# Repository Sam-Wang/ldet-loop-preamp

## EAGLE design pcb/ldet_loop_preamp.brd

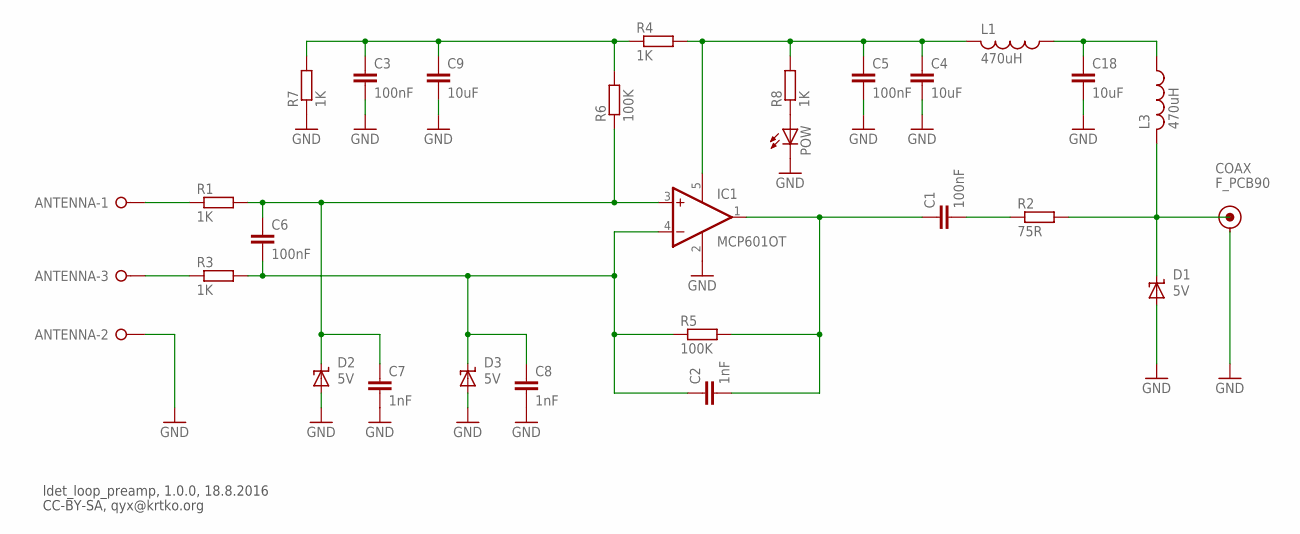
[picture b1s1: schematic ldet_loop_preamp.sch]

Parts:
ANTENNA: W237-3E
C1, C3, C5, C6: 100nF; C0603
C2, C7, C8: 1nF; C0603
C4, C9, C18: 10uF; C1206
COAX: F_PCB90; F_PCB_90
D1, D2, D3: 5V; SMBJ
IC1: MCP601OT; SOT23-5
L1, L3: 470uH; L3225M; MPN LQH32CN471K23L
POW: LEDCHIPLED_0603; CHIPLED_0603
R1, R3, R4, R7, R8: 1K; R0603
R2: 75R; R0603
R5, R6: 100K; R0603

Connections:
GND: ANTENNA.2, C3.2, C4.2, C5.2, C7.2, C8.2, C9.2, C18.2, COAX.S1 (SHIELD), COAX.S2 (SHIELD), COAX.S3 (SHIELD), COAX.S4 (SHIELD), D1.A, D2.A, D3.A, IC1.2 (V-), POW.C, R7.1
unnamed: COAX.C (CENTER), D1.C, L3.2, R2.2
unnamed: C1.2, R2.1
unnamed: C18.1, L1.1, L3.1
unnamed: C1.1, C2.2, IC1.1 (OUT), R5.2
unnamed: ANTENNA.3, R3.1
unnamed: C4.1, C5.1, IC1.5 (V+), L1.2, R4.2, R8.2
unnamed: C3.1, C9.1, R4.1, R6.2, R7.2
unnamed: POW.A, R8.1
unnamed: ANTENNA.1, R1.1
unnamed: C2.1, C6.2, C8.1, D3.C, IC1.4 (-IN), R3.2, R5.1
unnamed: C6.1, C7.1, D2.C, IC1.3 (+IN), R1.2, R6.1

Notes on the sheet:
ldet_loop_preamp, 1.0.0, 18.8.2016
CC-BY-SA, qyx@krtko.org

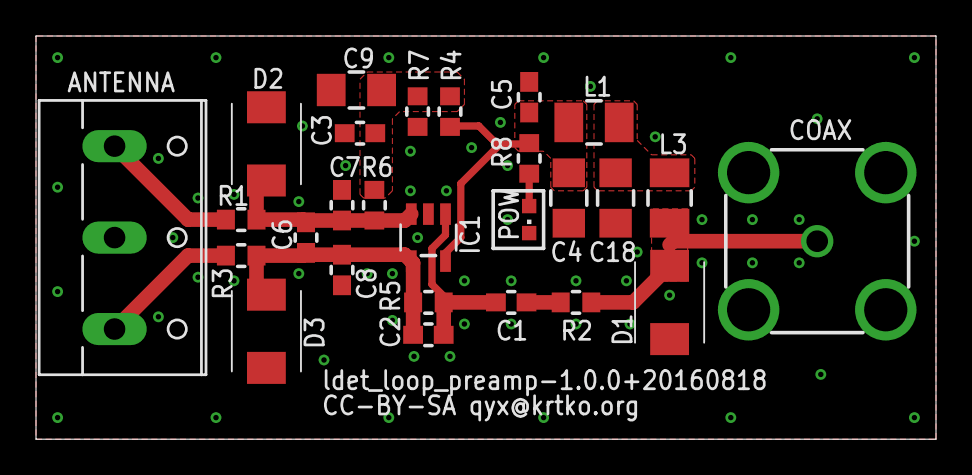
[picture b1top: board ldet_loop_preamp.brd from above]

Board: 2 copper layers, 50.0 x 22.4 mm, 27 parts (0 on the bottom side), 12 nets.

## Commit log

2016-08-18 Add preamp schematic and layout
